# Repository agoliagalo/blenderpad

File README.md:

# Blenderpad

A small, 18-key wireless-capable macropad built around the shortcuts I actually use in Blender, with a toggleable numpad layer for viewport navigation.

But the keyboard itself is only half of this project. **The real idea is that your Blender workflow is not mine.** Everyone uses different tools, different shortcuts, different hands. So this repository gives you the whole path, from measuring *your* habits to holding *your* keyboard:

1. **Measure** which keys you really press in Blender, with a small add-on.
2. **Design** a layout that fits those keys.
3. **Draw** the PCB, order it, solder it.
4. **Flash** a firmware and tweak your keymap until it feels right.

Take my files as a starting point, not as the answer. Change the number of keys, move them around, swap the shortcuts. Experiment!

---

## Repository contents

```
addon/        KeyPressTracker, the Blender add-on that counts your key presses
hardware/     KiCad project, production-ready Gerbers, 3D model, schematic PDF, BOM
boards/       ZMK shield definition (matrix, pins, keymap)
config/       ZMK configuration
docs/         Keymap customization guide and blank keymap template
images/       Photos used in this README
build.yaml    Tells GitHub which firmware to build
```

---

## Step 1 — Find your keys with KeyPressTracker

KeyPressTracker is a small Blender add-on that counts every key and shortcut you press, so you can base your layout on real data instead of guesses.

### Install

Requires Blender 4.2 or newer.

1. Download the `.py` file from [`addon/`](addon/).
2. In Blender, go to `Edit → Preferences → Add-ons`.
3. Click the small arrow in the top-right corner of the add-ons list. A menu opens: choose **Install from Disk**.
4. Select the `.py` file. KeyPressTracker appears in the list, already enabled.

### Save your .blend file first

**Save your Blender file before you start tracking.** By default, the results are written to `key_counts.csv`, **in the same folder as your .blend file**. If the file has never been saved, Blender doesn't know where that folder is, and the results can't be written. You can also pick another location with the **File** field in the panel.

### How it works

In the 3D viewport, open the sidebar (`N`) and go to the **KeyPressTracker** tab.

1. Click **Start**, then work in Blender exactly as usual. The status switches to *Running*.
2. Every key you press is counted, along with its modifiers: `G`, `Shift+A`, `Ctrl+Z`, `NUMPAD_7`... Mouse clicks and the automatic repeats of a held key are ignored.
3. The panel shows your top 10 live, and the total number of presses.
4. Click **Stop** when you're done: the counts are saved to the CSV file. **Save** writes the file at any time without stopping, **Reset** clears all counts (with confirmation).

Opening another .blend file stops the tracking. Just click **Start** again.

Let it run over several real working sessions, not a five-minute test: the more data, the more honest the result.

### What to do with the results

The CSV file has two columns, the key and the number of presses, sorted from most to least used. Open it in any spreadsheet (Excel, LibreOffice, Google Sheets).

- **The top of the list is your keyboard.** My 18 keys came from roughly the top of mine. Decide how many keys you want, and keep that many from the top.
- **Look at the modifiers.** If `Shift`, `Ctrl` or `Alt` show up a lot, alone or in combos, give them dedicated keys. A shortcut like `Shift+A` can also be a single key on its own.
- **Look at the numpad keys.** If `NUMPAD_1`, `NUMPAD_3`, `NUMPAD_7` rank high, you navigate the viewport with the numpad, and a numpad layer like mine is worth it.
- **Spot the surprises.** Some keys you thought you used all the time won't be there, and the other way around. That's exactly why this step exists.

Then group the keys by how you use them (transform, selection, modes, views...) and move on to the layout.

---

## Step 2 — Design a layout with Ergogen

Before committing to a PCB, I iterated on the layout with [Ergogen](https://ergogen.xyz/), which describes a keyboard in a text file. Writing a layout as code is intimidating at first, but it lets you change the number of keys or their spacing in seconds, and that freedom is exactly what you want at this stage.

This tutorial makes it click very quickly, I highly recommend it: **[Ergogen introduction by FlatFootFox](https://flatfootfox.com/ergogen-introduction/)**

Good to know: Ergogen's web preview shows key positions but not components like diodes or switches. You only see those once the output is opened in KiCad. I ended up doing the electronics directly in KiCad.

---

## Step 3 — Draw the PCB in KiCad

I learned to design a keyboard PCB in KiCad with this video, which I highly recommend: **[KiCad keyboard PCB tutorial](https://www.youtube.com/watch?v=8WXpGTIbxlQ&t=162s)**

All footprints and 3D models come from the excellent **[ScottoKicad library](https://github.com/joe-scotto/scottokeebs/tree/main/Extras/ScottoKicad)** by Joe Scotto. It is **not included** in this repository: install it yourself if you want to edit the design.

The KiCad files in [`hardware/kicad/`](hardware/kicad/) open without the library, because the PCB file keeps a copy of every footprint. You only need ScottoKicad to add new parts, update footprints, or see the 3D view (the 3D models use the `${SCOTTOKEEBS_KICAD}` path variable, which the library's install guide explains how to set).

**Just want to build mine?** [`hardware/gerbers/`](hardware/gerbers/) contains the production-ready files. Upload the `.zip` to any PCB manufacturer (JLCPCB, PCBWay...). Standard settings: 2 layers, 1.6 mm.

Also in [`hardware/`](hardware/): the schematic as a PDF, a STEP model to design a case around the PCB, and the [bill of materials](hardware/BOM.md).

### The matrix

18 keys wired as a 6 columns × 4 rows matrix, one 1N4148 diode per key, `col2row` orientation (the diode's cathode, the black band, points to the row).

| | col 1 | col 2 | col 3 | col 4 | col 5 | col 6 |
|---|---|---|---|---|---|---|
| row 1 | S1 | S2 | S3 | S4 | | |
| row 2 | S5 | S6 | S7 | S8 | | |
| row 3 | S9 | S10 | S11 | S12 | | |
| row 4 | S13 | S14 | S15 | S16 | S17 | S18 |

Controller pins (Pro Micro labels, as printed on the PCB): columns 1–6 on `21, 20, 19, 18, 15, 14`, rows 1–4 on `4, 5, 2, 3`.

---

## Step 4 — Build it

**Parts:** see the [BOM](hardware/BOM.md). Kailh Choc V1 switches, 1N4148 through-hole diodes, and a nice!nano v2 or a compatible clone.

**Soldering order:** diodes first (flattest), then the controller, then the switches last, so they don't block access to everything else. Solder one leg of each diode, check it sits flat and in the right direction, then solder the second.

**Before the first power-on:** inspect for solder bridges, especially on the controller. If you have a multimeter, check there is **no** continuity between `GND` and `3.3v`.

---

## Step 5 — Flash the firmware (ZMK)

The firmware is built automatically by GitHub, no installation needed.

1. **Fork** this repository. GitHub Actions builds the firmware on every push.
2. Open the **Actions** tab, select the latest green run, and download the file under **Artifacts**. Unzip it to get a `.uf2` file.
3. Plug the keyboard in via USB and enter flash mode: short **`RST` to `GND` twice quickly** (tweezers or a piece of wire work fine; the two holes are next to each other on the PCB). A drive named `NICENANO` appears.
4. Drag the `.uf2` onto that drive. It disconnects by itself when done: that's normal.

Once the firmware is installed, the bootloader key on the numpad layer does step 3 for you.

### Default keymap

The firmware sends **positions**, not letters (see the AZERTY pitfall below). The labels here are what you get with a **French AZERTY** layout on the computer.

```
Main layer                       Numpad layer (toggled)
M    B    A    D                 1    2    3    4
X    Y    Z    G                 5    6    7    8
S    E    I    R                 9    0    .    Enter
Alt  Num  N    Shift Ctrl Tab    Alt  Num  BOOT Shift Ctrl Tab
```

`Num` toggles the numpad layer on and off. The numbers are **numpad** keys, the ones Blender uses for viewport views.

**Make it yours:** the [customization guide](docs/customize.md) explains the keymap syntax, and [`docs/template.keymap`](docs/template.keymap) is a blank template to start from.

---

## Numpad indicator: using the controller's LED

The red LED on the SuperMini (and on the nice!nano) is a *user LED* wired to GPIO `P0.15`. This project uses it as a numpad layer indicator, without adding any component, thanks to the small [zmk-led-indicator](https://github.com/northwestisthebest/zmk-led-indicator) module.

Two pieces make it work:

- [`config/west.yml`](config/west.yml) declares the module (with `revision: main`, since the module has no ZMK-version branches).
- The shield overlay declares the LED and the layer it watches:

```dts
led_indicator: led_indicator {
    compatible = "zmk,led-indicator";
    gpios = <&gpio0 15 GPIO_ACTIVE_HIGH>;
    indicate-layer = <1>;
};
```

The **blue** LED on the SuperMini is hardwired to the battery charger and cannot be controlled. Without a battery, it blinks forever. A piece of tape does the trick.

---

## Beginner pitfalls (I fell into all of them)

**Using a clone instead of a nice!nano.** The SuperMini nRF52840 is a cheap clone with the same pinout, and it works with the `nice_nano_v2` board in ZMK. But it has **13 pins per side** instead of 12: the two extra pins at the top, `B+` and `B−` (battery), hang over the edge of a nice!nano footprint. Align the rest (`GND` in `GND`, `RST` in `RST`) and **check the alignment before soldering**. Its three extra bottom pins don't match the nice!nano's either: leave them alone.

**AZERTY (and other non-QWERTY layouts).** ZMK sends key *positions* as if the computer were in QWERTY, and the operating system translates them. With a French AZERTY layout, `&kp Q` types **A**, `&kp W` types **Z**, and `&kp SEMI` types **M** (and the other way around for A and Z). Write your keymap accordingly and test a few keys after flashing.

**Num Lock.** Numpad keys only produce numbers if Num Lock is on in the operating system. Otherwise they act as Home, End, arrows... and in Blender, Home means "frame all". Num Lock is a system-wide state, so turning it on once (from another keyboard or the on-screen keyboard) is enough.

**Tracks that refuse to enter a footprint in KiCad.** If a track stops dead at the outline of a module, the footprint probably contains **Rule Areas** (keepout zones). Check in the footprint editor and remove them if they're not needed.

**KiCad libraries outside the project folder.** They won't exist on anyone else's computer. Keep project-specific libraries inside the project folder and reference them with `${KIPRJMOD}`.

**Diode direction.** All diodes must face the same way, black band towards the row. If you soldered all of them backwards, no need to desolder: change `diode-direction` to `"row2col"` in the overlay.

**Charge-only USB cables.** The keyboard lights up but the computer doesn't see it. Use a cable that carries data.

**Editing ZMK files with Notepad.** Save as *All files* with UTF-8 encoding, and check that Windows didn't silently add `.txt` to the file name.

---

## Licenses

- **Add-on** ([`addon/`](addon/)): GPL-3.0-or-later, as required for Blender add-ons.
- **Firmware configuration**: MIT, like ZMK itself.
- **Hardware** ([`hardware/`](hardware/)): CC BY-NC-SA 4.0, matching the ScottoKicad footprints it is built on. You may build, modify and share it, but not sell it.

## Credits

- [ScottoKicad](https://github.com/joe-scotto/scottokeebs/tree/main/Extras/ScottoKicad) by Joe Scotto, for every footprint and 3D model (CC BY-NC-SA 4.0).
- The [KiCad keyboard tutorial](https://www.youtube.com/watch?v=8WXpGTIbxlQ&t=162s) that taught me PCB design.
- [FlatFootFox's Ergogen introduction](https://flatfootfox.com/ergogen-introduction/).
- [ZMK Firmware](https://zmk.dev/) and [zmk-led-indicator](https://github.com/northwestisthebest/zmk-led-indicator).

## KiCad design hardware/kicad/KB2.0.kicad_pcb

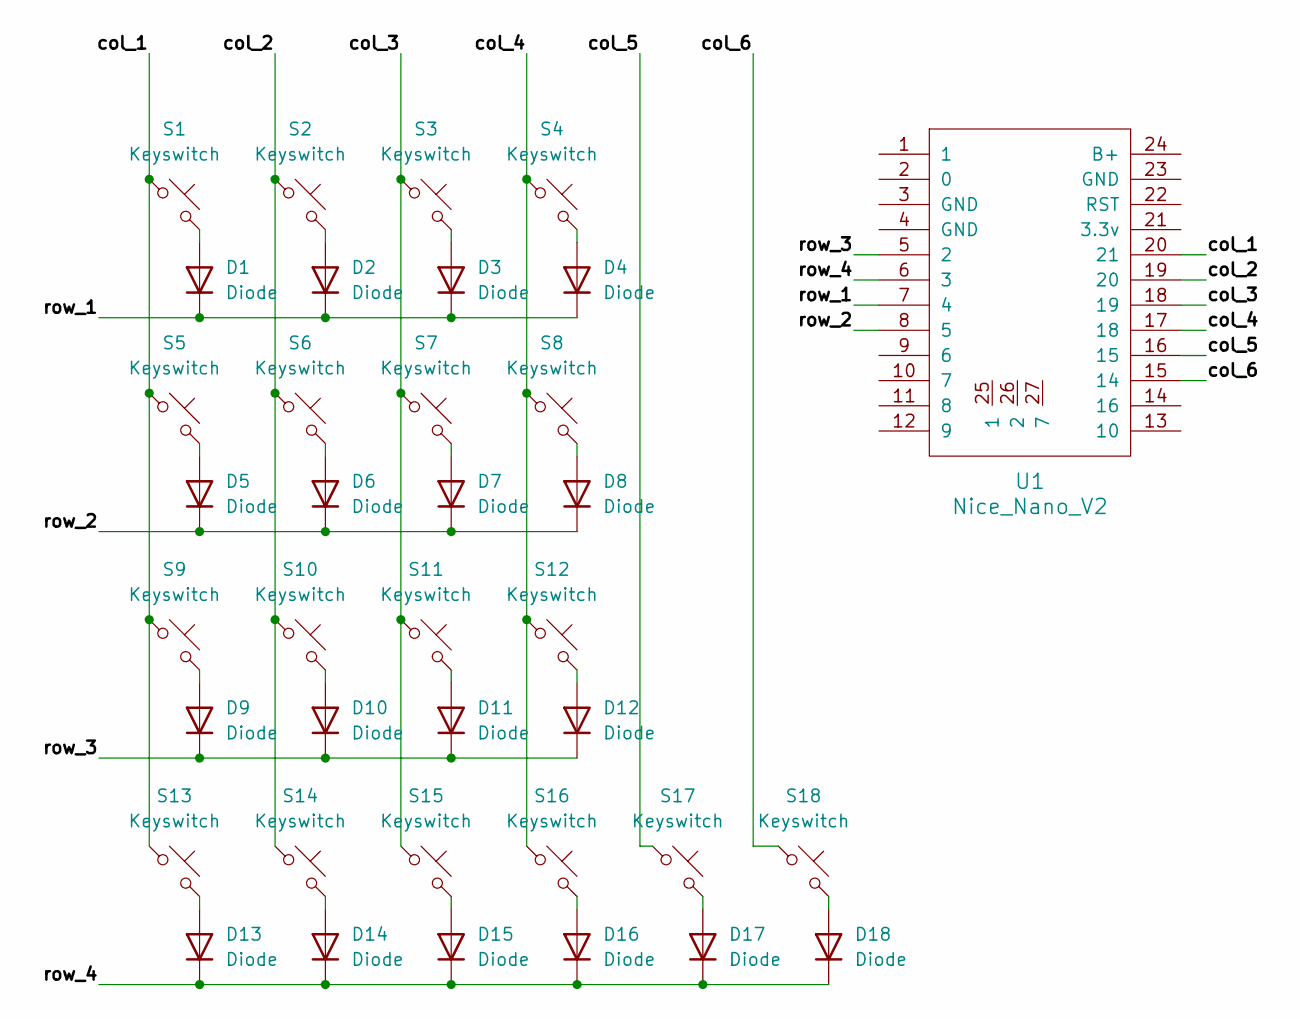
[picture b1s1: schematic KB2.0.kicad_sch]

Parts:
D1, D2, D3, D4, D5, D6, D7, D8, D9, D10, D11, D12, D13, D14, D15, D16, D17, D18: Diode; Diode_DO-35
S1, S2, S3, S4, S5, S6, S7, S8, S9, S10, S11, S12, S13, S14, S15, S16, S17, S18: Keyswitch; Choc_V1
U1: Nice_Nano_V2

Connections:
/col_1: S1.1, S5.1, S9.1, S13.1, U1.20 (21)
/col_2: S2.1, S6.1, S10.1, S14.1, U1.19 (20)
/col_3: S3.1, S7.1, S11.1, S15.1, U1.18 (19)
/col_4: S4.1, S8.1, S12.1, S16.1, U1.17 (18)
/col_5: S17.1, U1.16 (15)
/col_6: S18.1, U1.15 (14)
/row_1: D1.1 (K), D2.1 (K), D3.1 (K), D4.1 (K), U1.7 (4)
/row_2: D5.1 (K), D6.1 (K), D7.1 (K), D8.1 (K), U1.8 (5)
/row_3: D9.1 (K), D10.1 (K), D11.1 (K), D12.1 (K), U1.5 (2)
/row_4: D13.1 (K), D14.1 (K), D15.1 (K), D16.1 (K), D17.1 (K), D18.1 (K), U1.6 (3)
unnamed: D1.2 (A), S1.2
unnamed: D2.2 (A), S2.2
unnamed: D3.2 (A), S3.2
unnamed: D4.2 (A), S4.2
unnamed: D5.2 (A), S5.2
unnamed: D6.2 (A), S6.2
unnamed: D7.2 (A), S7.2
unnamed: D8.2 (A), S8.2
unnamed: D9.2 (A), S9.2
unnamed: D10.2 (A), S10.2
unnamed: D11.2 (A), S11.2
unnamed: D12.2 (A), S12.2
unnamed: D13.2 (A), S13.2
unnamed: D14.2 (A), S14.2
unnamed: D15.2 (A), S15.2
unnamed: D16.2 (A), S16.2
unnamed: D17.2 (A), S17.2
unnamed: D18.2 (A), S18.2

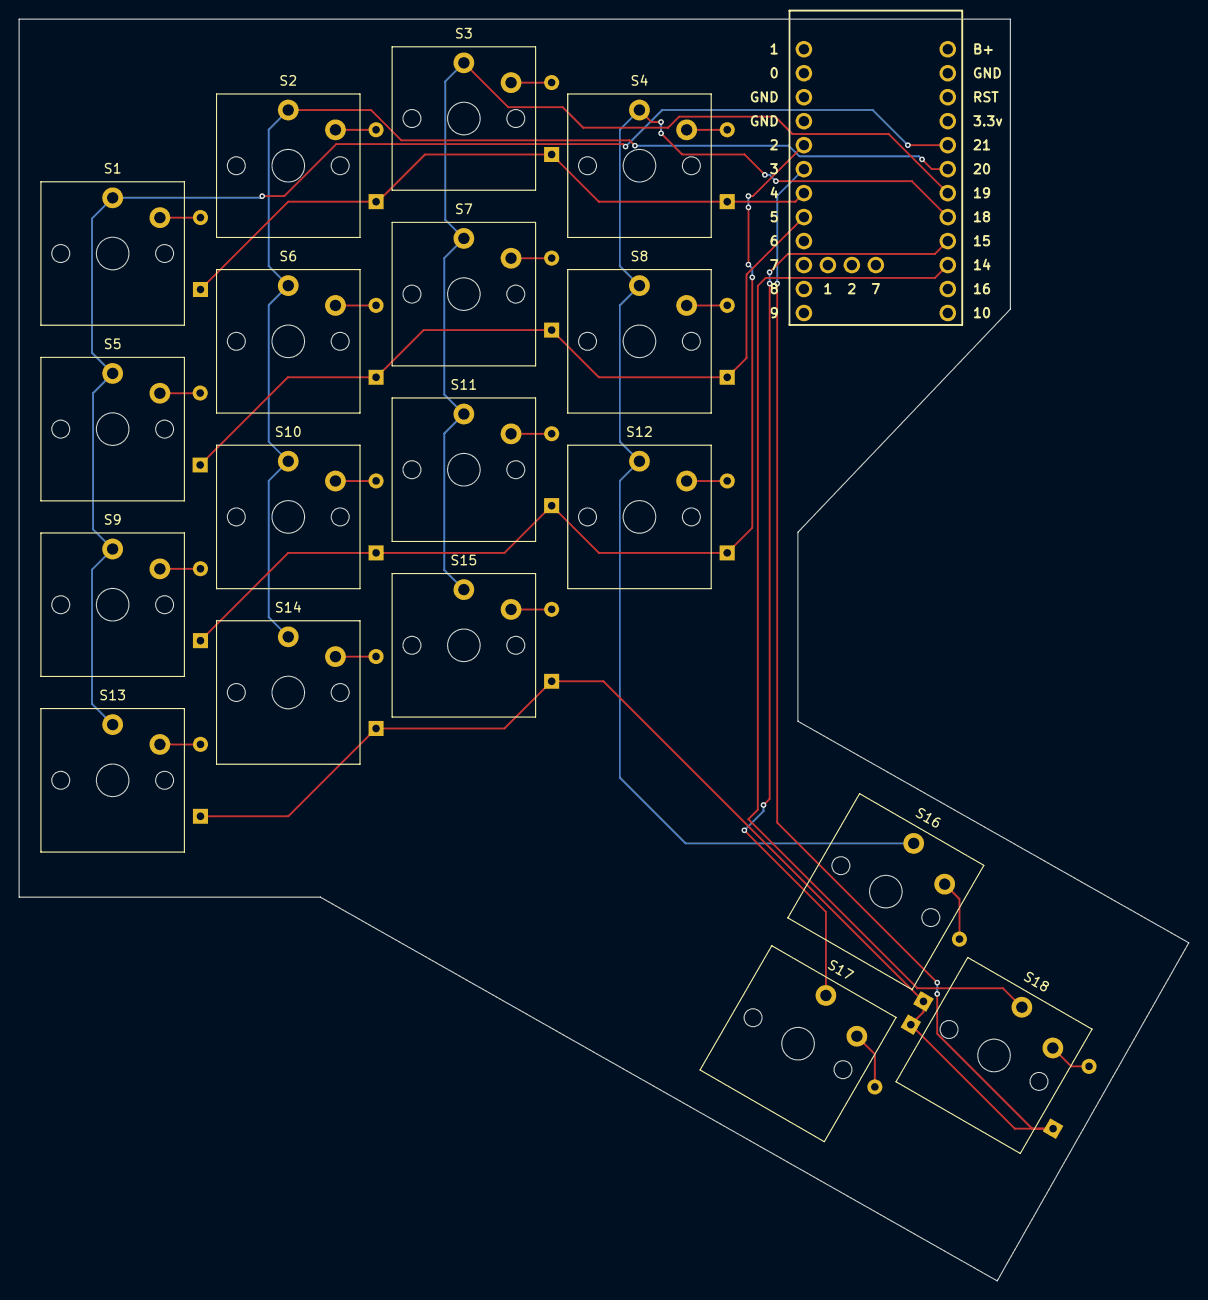
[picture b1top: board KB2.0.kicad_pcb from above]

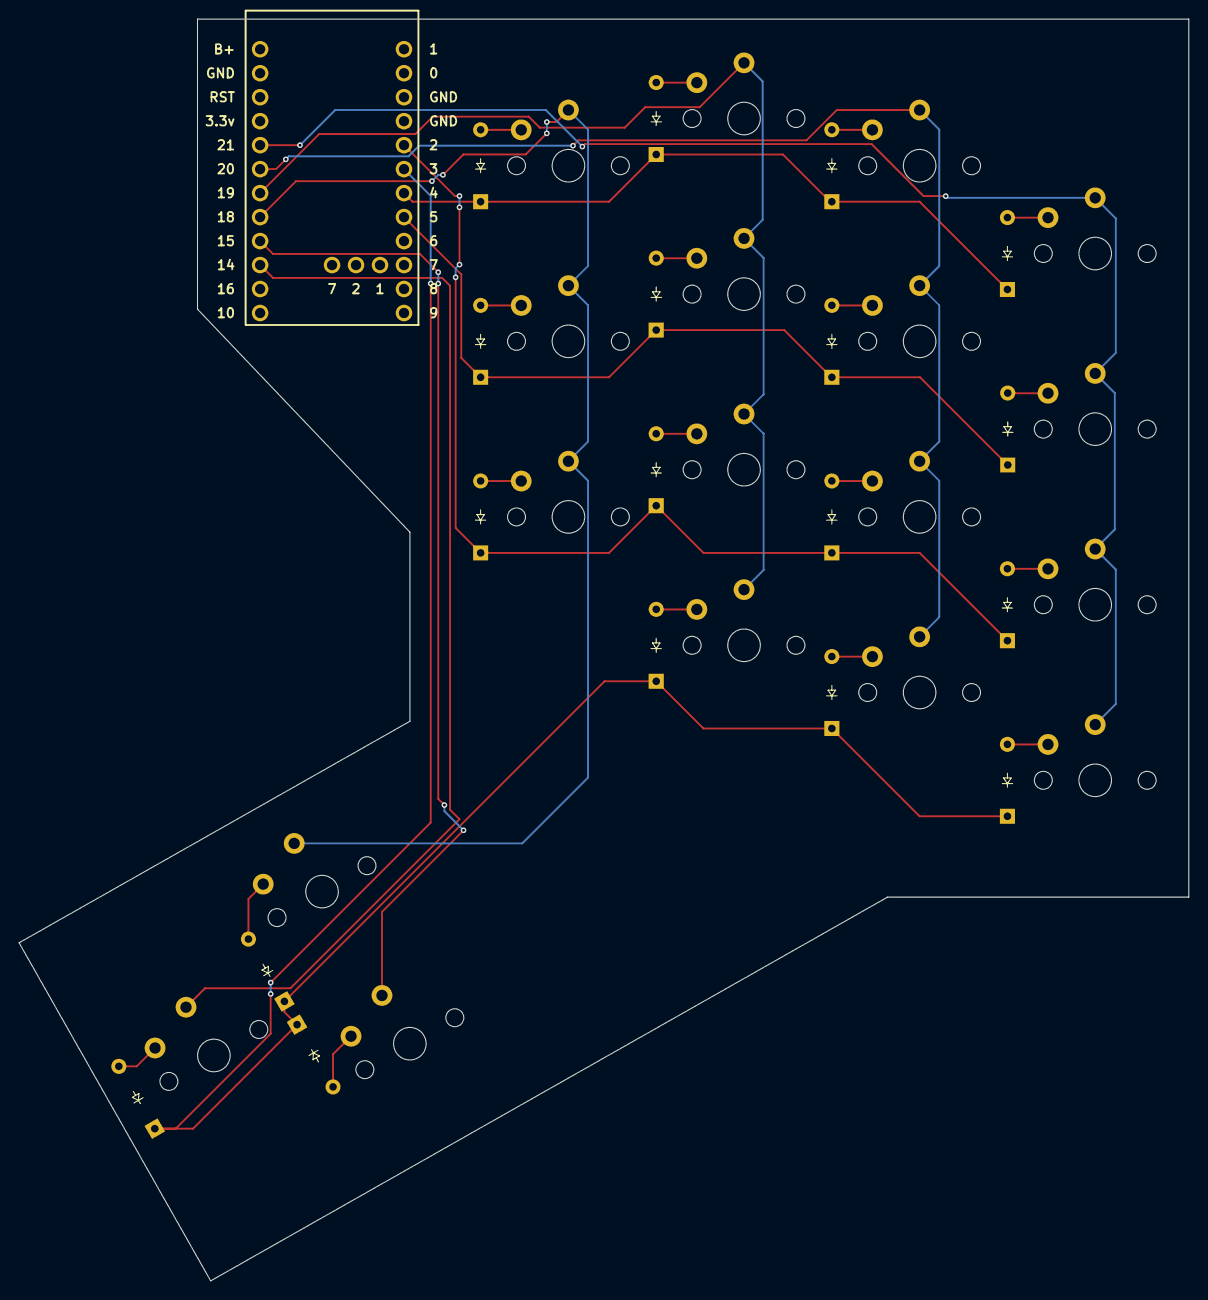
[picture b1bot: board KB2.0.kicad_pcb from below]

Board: 2 copper layers, 123.9 x 133.7 mm, 37 parts (18 on the bottom side), 28 nets.

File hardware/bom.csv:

Designator,Footprint,Quantity,Value,LCSC Part #
"D1, D10, D11, D12, D13, D14, D15, D16, D17, D18, D2, D3, D4, D5, D6, D7, D8, D9",Diode_DO-35,18,Diode,
"S1, S10, S11, S12, S13, S14, S15, S16, S17, S18, S2, S3, S4, S5, S6, S7, S8, S9",Choc_V1,18,Keyswitch,
U1,Nice_Nano_V2,1,Nice_Nano_V2,
